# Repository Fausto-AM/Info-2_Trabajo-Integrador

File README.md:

# Trabajo Práctico Integrador - Máquinas de Estado

Repositorio personal para la entrega del Trabajo Práctico Integrador de Informática II para la UTNFRA.

## Profesores

- Ing. Gustavo Viard.
- Mg. Ing. Damian Ruben Corbalan.

## Generador de Funciones con ESP32

### Resumen

El proyecto consiste en el diseño e implementación de un generador de funciones digital basado en un microcontrolador ESP32-WROOM.

El sistema permite seleccionar la forma de onda y modificar sus principales parámetros mediante un único encoder rotativo con pulsador. La información correspondiente al estado del generador, la función seleccionada y los parámetros configurables se presenta en una pantalla OLED SSD1306 de 128 × 64 píxeles.

La señal de salida es generada digitalmente mediante tablas de consulta (_Look-Up Tables_ [LUT]) y posteriormente convertida a una señal analógica mediante el DAC interno del ESP32. La generación de muestras se realiza a una frecuencia de muestreo de 40 kHz.

El firmware se encuentra organizado en módulos independientes y utiliza una máquina de estados finitos para gestionar la interfaz de usuario y los diferentes modos de operación del generador.

### Objetivos

- Implementar un generador de funciones digital utilizando el DAC interno del ESP32.
- Generar diferentes formas de onda: seno, cuadrada, triangular y sierra.
- Permitir la modificación de frecuencia, amplitud, offset y ciclo de trabajo.
- Permitir la modificación de los parámetros mientras la señal se encuentra siendo generada.
- Implementar una interfaz de usuario utilizando únicamente un encoder rotativo con pulsador.
- Visualizar el estado del sistema y los parámetros configurables mediante una pantalla OLED.
- Implementar una máquina de estados finitos que gestione la navegación y las acciones del usuario.
- Separar las diferentes funciones del firmware en módulos independientes.
- Generar las muestras de salida mediante una frecuencia de muestreo fija de 40 kHz.

### Diseño de la FSM

La interfaz de usuario se implementa mediante una máquina de estados finitos (FSM) contenida en `generator.c` y `generator.h`.

Los eventos producidos por el encoder son:

- `ENC_CW`: giro horario.
- `ENC_CCW`: giro antihorario.
- `ENC_SHORT_PRESS`: pulsación corta.
- `ENC_LONG_PRESS`: pulsación larga.

#### Estados

- `STATE_STANDBY`

    Es el estado inicial de operación del generador.

    La salida se encuentra detenida y el usuario puede desplazarse mediante el encoder entre las siguientes opciones:

    * Parámetros
    * Función
    * RUN

    Una pulsación corta confirma la opción seleccionada.

    Al seleccionar _RUN_, el sistema pasa a `STATE_GENERATING`.

- `STATE_GENERATING`

    En este estado el generador se encuentra funcionando y el DAC recibe las muestras generadas.

    El menú principal pasa a mostrar:

    * Parámetros
    * Función
    * STOP

    Desde este estado también es posible ingresar a los menús de parámetros y selección de función sin detener la generación de la señal.

    Al seleccionar _STOP_, el sistema vuelve a `STATE_STANDBY`.

- `STATE_SELECT_PARAM`

    Permite seleccionar uno de los cuatro parámetros configurables:

    * Frecuencia
    * Amplitud
    * Offset
    * Duty

    Una pulsación corta sobre un parámetro lleva a `STATE_EDIT_PARAM`.

    Una pulsación larga abandona el menú y retorna al estado desde el cual se ingresó.

- `STATE_EDIT_PARAM`

    Permite modificar el parámetro seleccionado mediante el giro del encoder.

    Cada parámetro posee:

    * un valor actual;
    * un límite mínimo;
    * un límite máximo;
    * un tamaño de paso;
    * una función setter encargada de aplicar el nuevo valor.

    Los valores se limitan automáticamente a los rangos definidos en config.h.

    Una pulsación corta o larga finaliza la edición y retorna a `STATE_SELECT_PARAM`.

- `STATE_SELECT_FUNC`

    Permite seleccionar la forma de onda utilizada por el generador:

    * Seno
    * Cuadrada
    * Triangular
    * Sierra

    Una pulsación corta aplica inmediatamente la función seleccionada. Esto permite recorrer las diferentes formas de onda y observar el cambio sin abandonar el menú.

    Una pulsación larga retorna al estado desde el cual se ingresó.

### Descripción de archivos

| Archivo | Responsabilidad |
|---|---|
| main.c | Punto de entrada de la aplicación. Inicializa el sistema y ejecuta el bucle principal de _polling_.
| sys.c/.h | Inicialización general de los módulos y procesamiento de eventos del sistema.
| generator.c/.h | Implementación de la máquina de estados, navegación de menús, selección de parámetros y control `RUN/STOP`.
| encoder.c/.h | Lectura del encoder y del pulsador. Genera los eventos utilizados por la FSM.
| display.c/.h | Control y actualización de la pantalla OLED mediante u8g2 e I2C.
| waveform.c/.h | Generación de las LUT, selección de formas de onda, acumulador de fase y cálculo de muestras.
| dac.c/.h | Abstracción del DAC interno del ESP32 mediante dac_oneshot.
| sample_timer.c/.h | Temporización de la generación de muestras mediante `esp_timer`.
| config.h | Configuración de GPIO, límites de parámetros, frecuencia de muestreo y constantes del sistema.

### Diagrama de la Máquina de Estado

### Esquemático

### PCB Finalizado

### Proyecto Funcionando

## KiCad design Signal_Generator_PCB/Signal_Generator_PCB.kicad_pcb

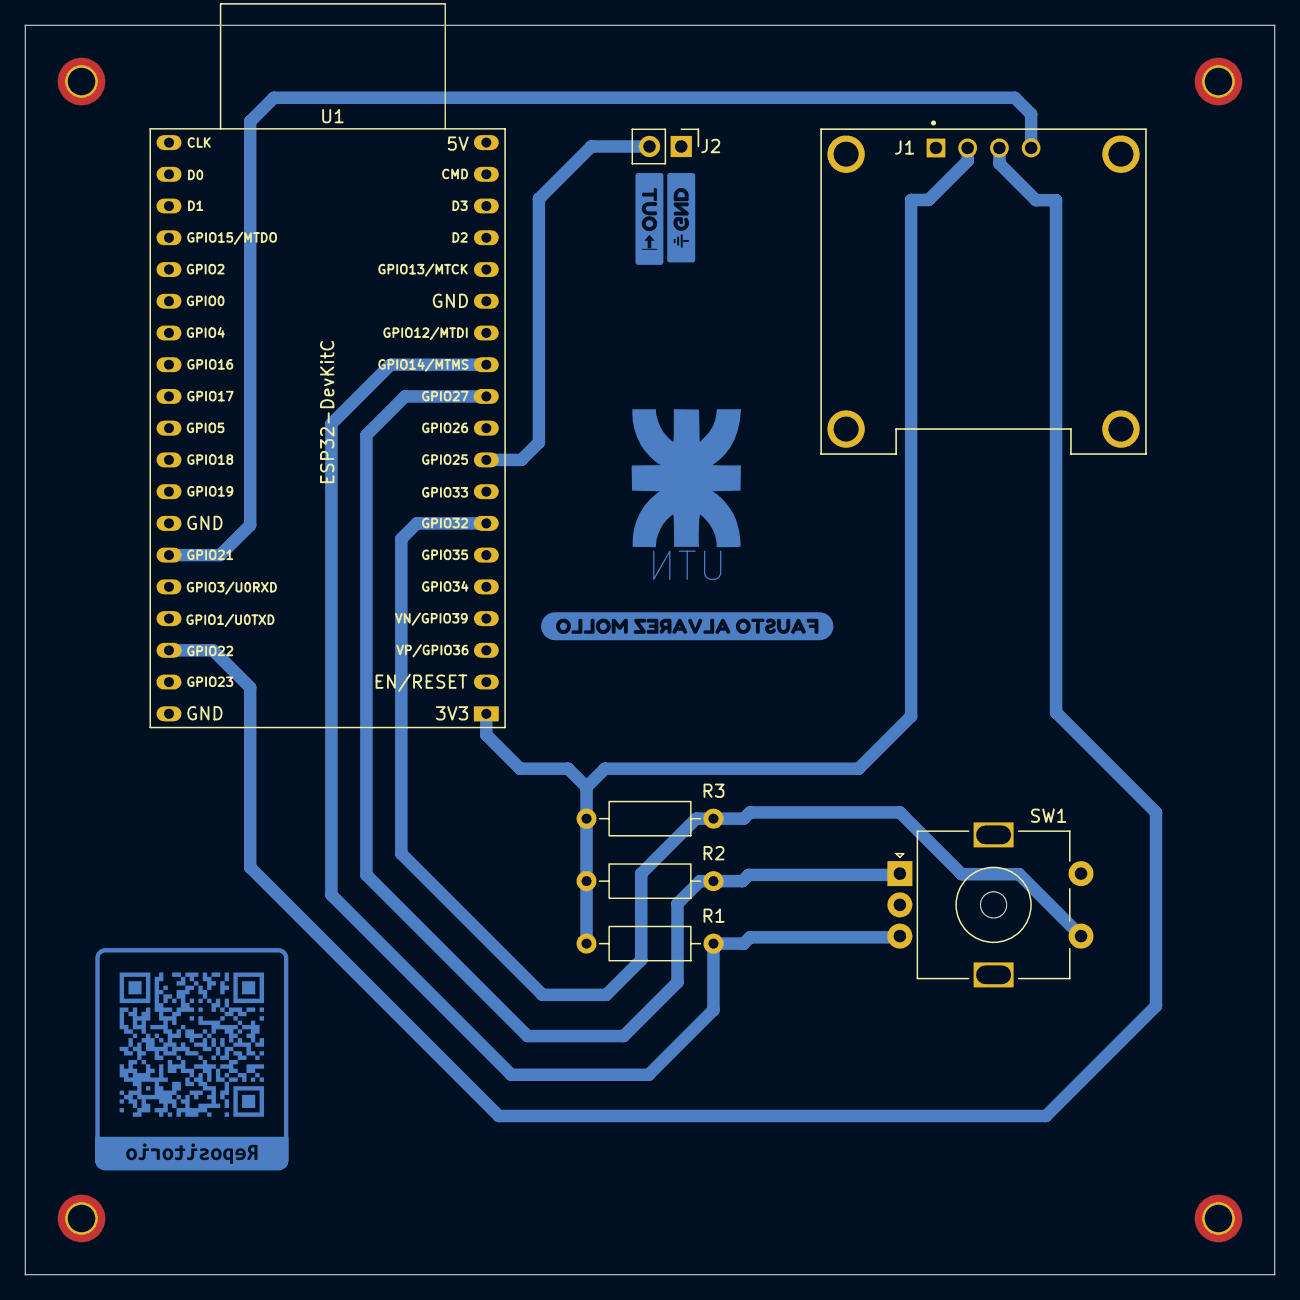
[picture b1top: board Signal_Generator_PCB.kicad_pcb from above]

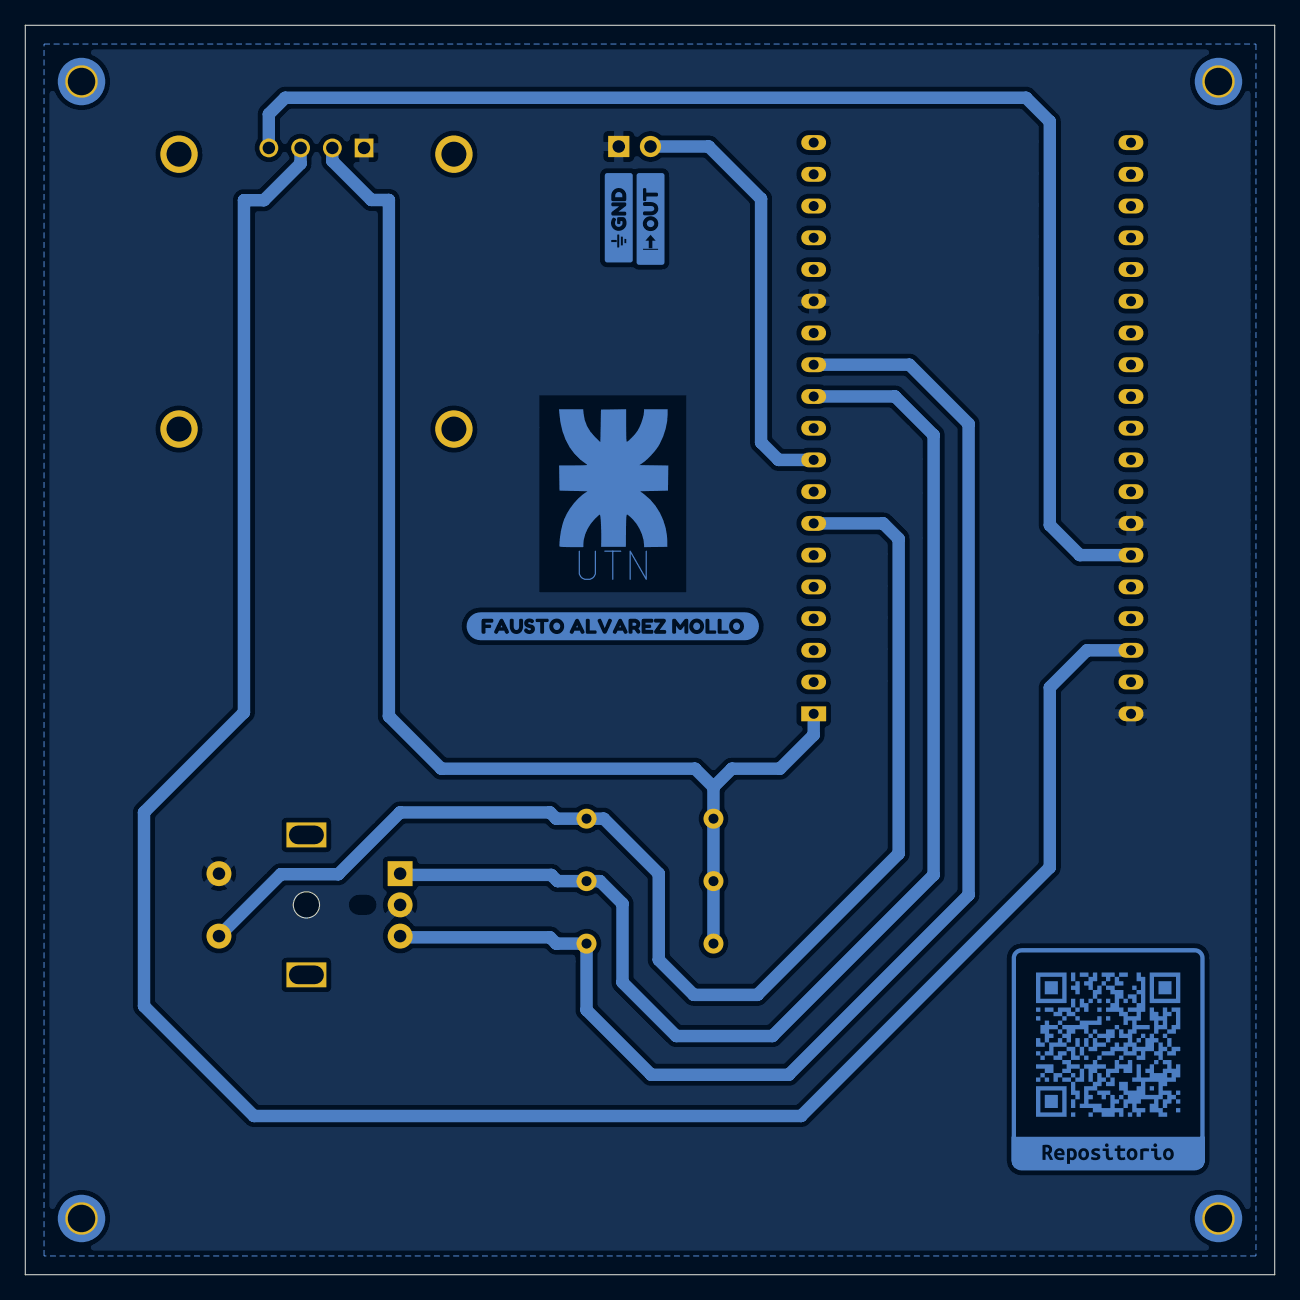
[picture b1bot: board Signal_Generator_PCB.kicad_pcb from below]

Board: 2 copper layers, 100.0 x 100.0 mm, 11 parts (4 on the bottom side), 8 nets.

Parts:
J1: OLED Screen; MODULE_DM-OLED096-636
J2: Conn_01x02; PinHeader_1x02_P2.54mm_Vertical
R1, R2, R3: 10k; R_Axial_DIN0207_L6.3mm_D2.5mm_P10.16mm_Horizontal
SW1: Rotary Encoder with Switch; RotaryEncoder_Alps_EC11E-Switch_Vertical_H20mm_MountingHoles
U1: ESP32-DevKitC
kobee-studio-6AAF5AC9: Kobee Studio; kobee-studio-6AAF5ABC
kobee-studio-6AAF54B1: Kobee Studio; kobee-studio-6AAF52F9
kobee-studio-6AAF59F9: Kobee Studio; kobee-studio-6AAF59EB
kobee-studio-6AAF543E: Kobee Studio; kobee-studio-6AAF5432

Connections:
+3.3V: J1.2 (VDD), R1.2, R2.2, R3.2, U1.1 (3V3)
/GPIO14: R1.1, SW1.B, U1.12 (MTMS/GPIO14/ADC2_CH6)
/GPIO21: J1.4 (SDA), U1.33 (GPIO21)
/GPIO22: J1.3 (SCK), U1.36 (GPIO22)
/GPIO25: J2.1, U1.9 (DAC_1/ADC2_CH8/GPIO25)
/GPIO27: R2.1, SW1.A, U1.11 (ADC2_CH7/GPIO27)
/GPIO32: R3.1, SW1.S1, U1.7 (32K_XP/GPIO32/ADC1_CH4)
GND: J1.1 (GND), J2.2, SW1.C, SW1.S2, U1.14 (GND), U1.32 (GND), U1.38 (GND)
